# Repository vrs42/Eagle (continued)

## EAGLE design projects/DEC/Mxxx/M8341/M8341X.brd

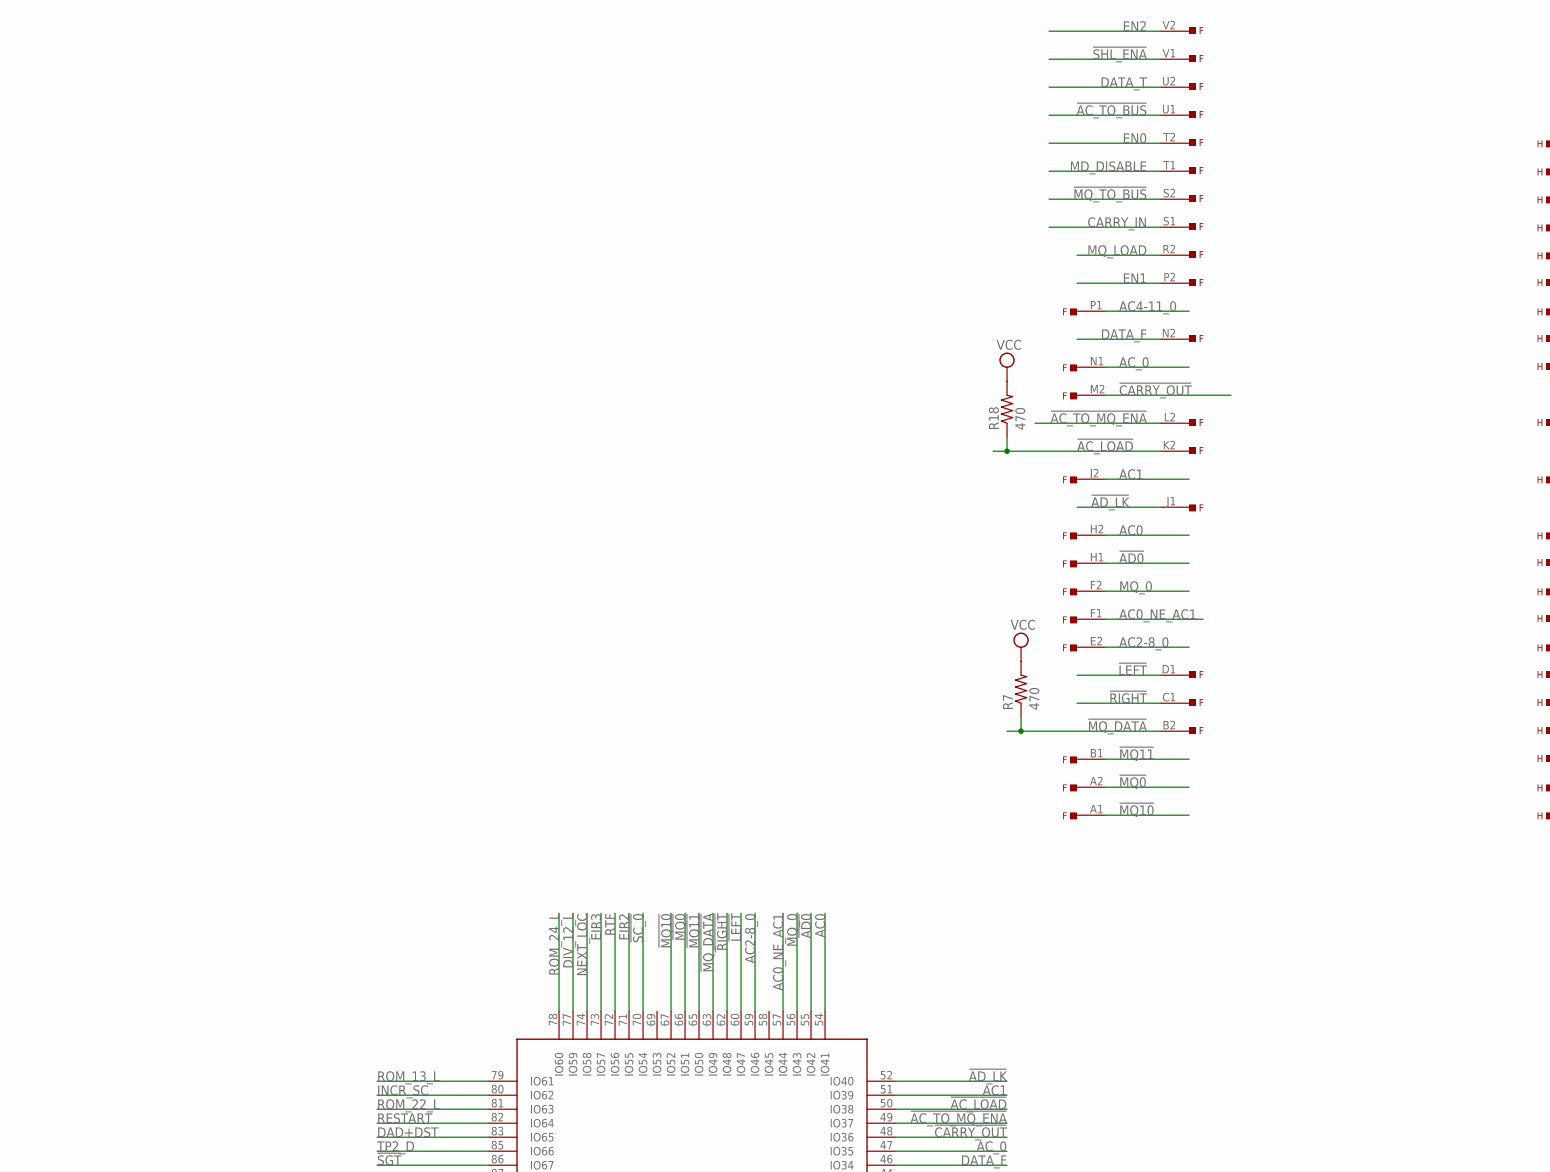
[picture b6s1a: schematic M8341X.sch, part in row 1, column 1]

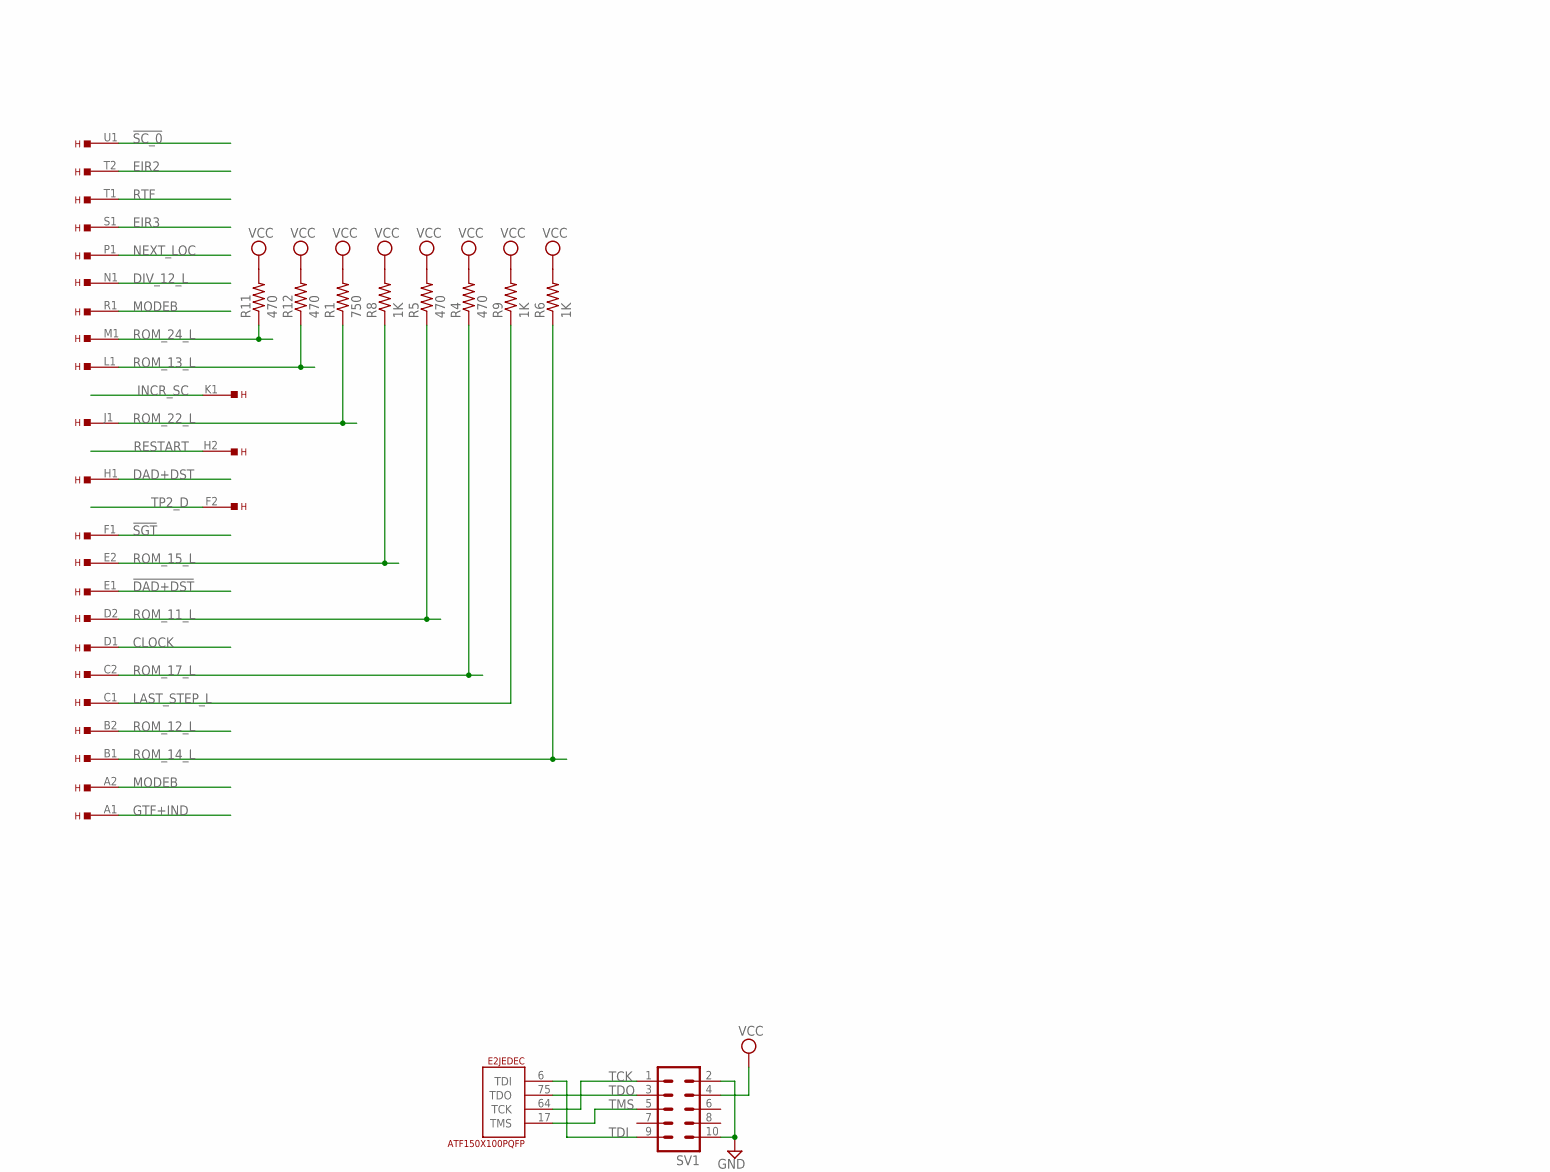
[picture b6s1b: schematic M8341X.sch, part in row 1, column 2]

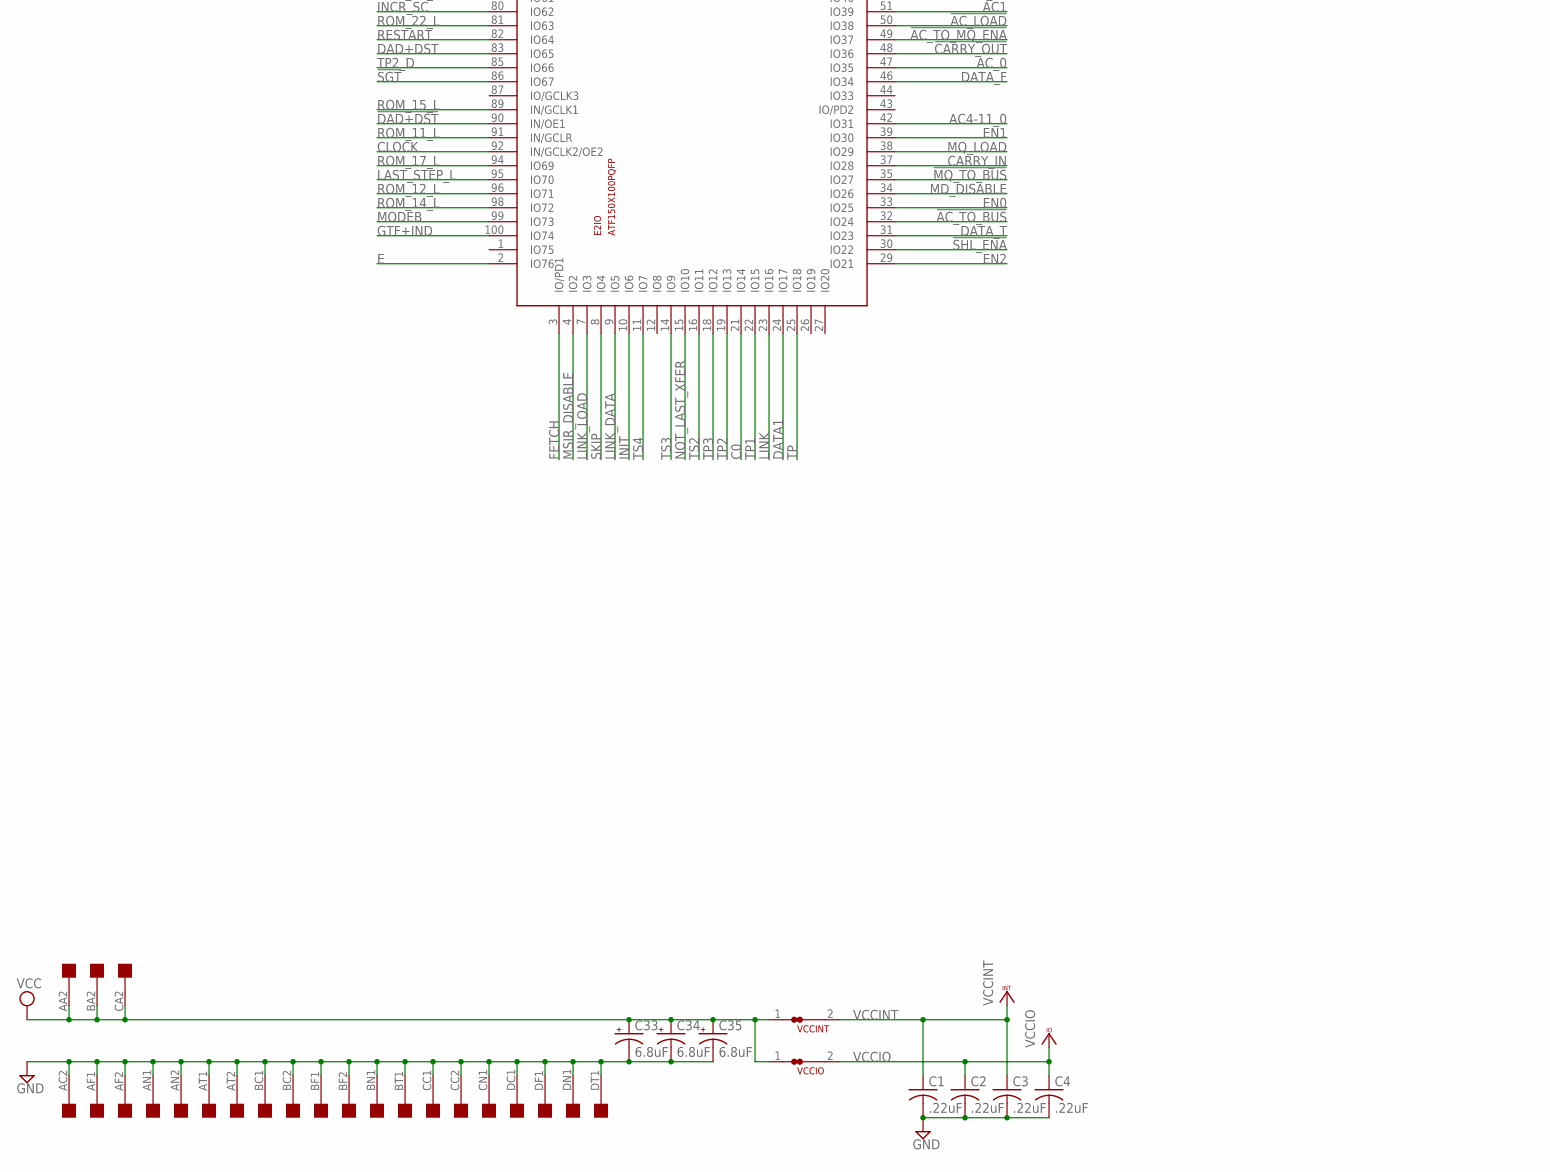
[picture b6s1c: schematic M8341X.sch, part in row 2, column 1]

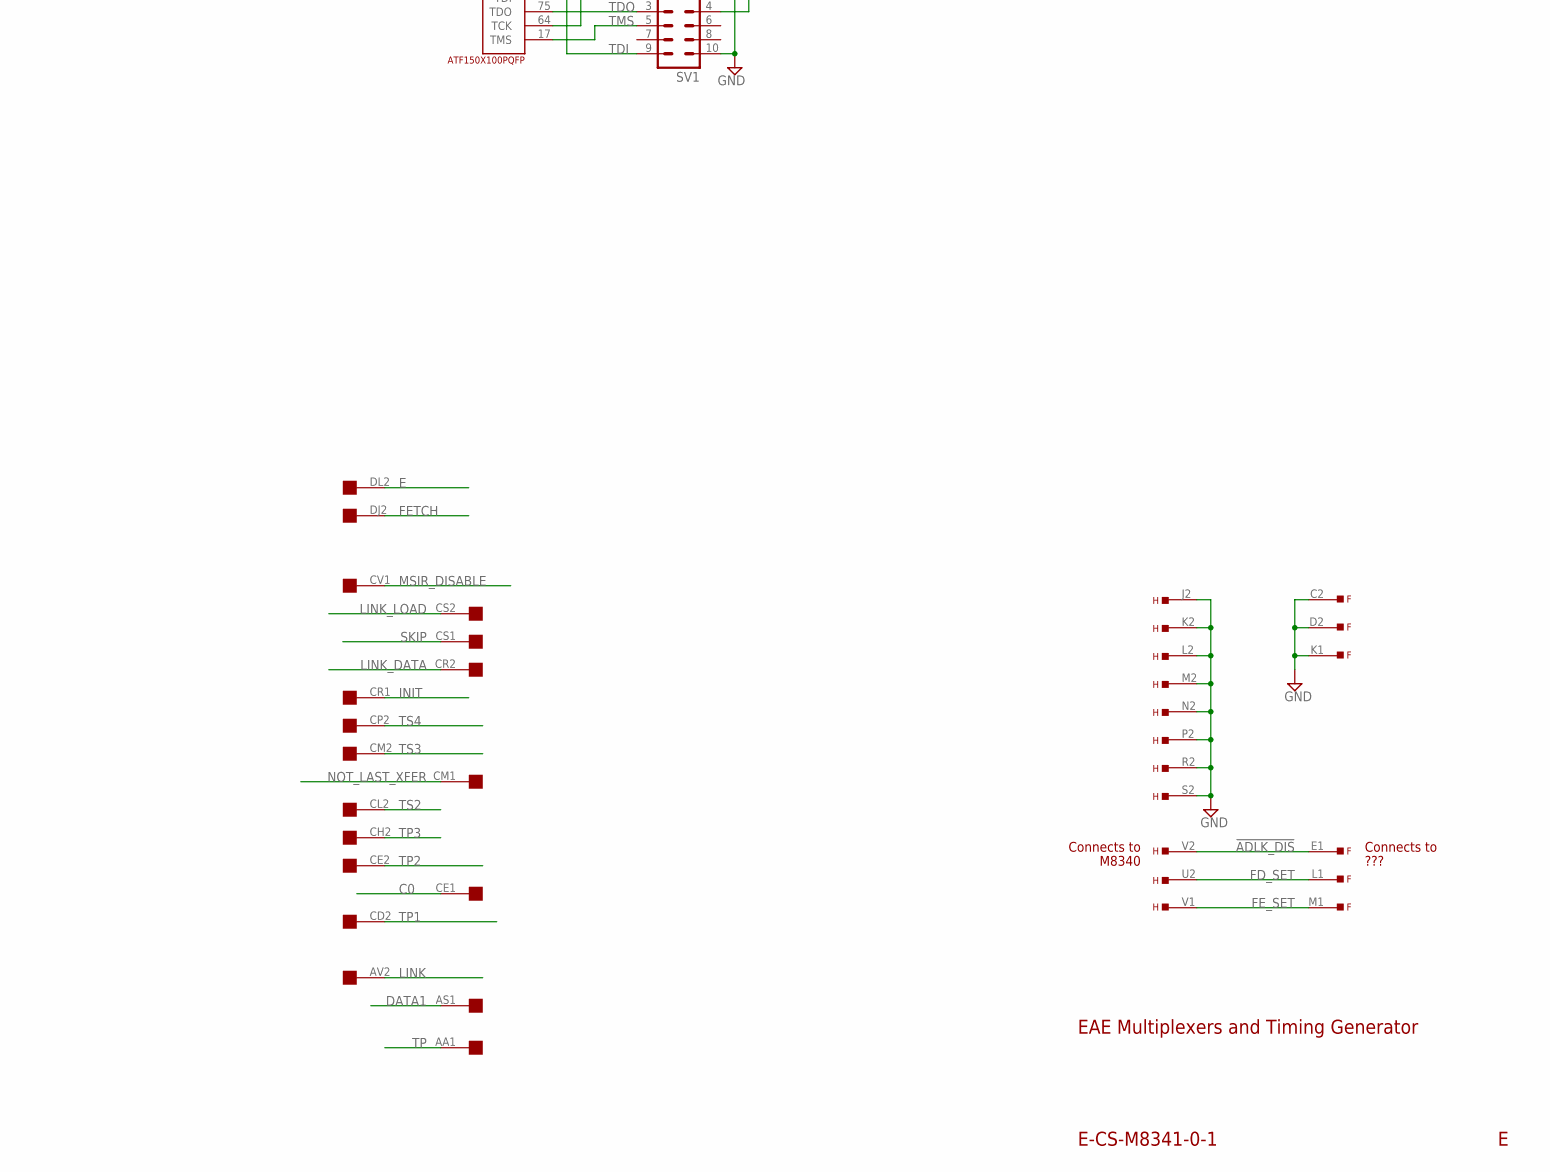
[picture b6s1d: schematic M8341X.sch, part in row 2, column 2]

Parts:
C1, C2, C3, C4: .22uF; C063-025X075
C33, C34, C35: 6.8uF; E12-8
E2: ATF150X100PQFP; PQFP-100
F: EDGE-TOP; EDGE-CON2
H: EDGE-TOP; EDGE-CON2
R1: 750; 0207/10
R4, R5, R7, R11, R12, R18: 470; 0207/10
R6, R8, R9: 1K; 0207/10
SV1: ML10
U$2: QUAD; EDGE-CON8
VCCINT: JUMPER-NC1; NC1
VCCIO: JUMPER-NC1; NC1

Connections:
!AC_LOAD: E2.50 (IO38), F.K2, R18.1
!AC_TO_BUS: E2.32 (IO24), F.U1
!AC_TO_MQ_ENA: E2.49 (IO37), F.L2
!AD0: E2.55 (IO42), F.H1
!ADLK_DIS: F.E1, H.V2
!AD_LK: E2.52 (IO40), F.J1
!CARRY_OUT: E2.48 (IO36), F.M2
!DAD+DST: E2.90 (IN/OE1), H.E1
!LEFT: E2.60 (IO47), F.D1
!MQ0: E2.66 (IO51), F.A2
!MQ10: E2.67 (IO52), F.A1
!MQ11: E2.65 (IO50), F.B1
!MQ_DATA: E2.63 (IO49), F.B2, R7.1
!MQ_TO_BUS: E2.35 (IO27), F.S2
!RIGHT: E2.62 (IO48), F.C1
!SC_0: E2.70 (IO54), H.U1
!SGT: E2.86 (IO67), H.F1
!SHL_ENA: E2.30 (IO22), F.V1
AC0: E2.54 (IO41), F.H2
AC0_NE_AC1: E2.57 (IO44), F.F1
AC1: E2.51 (IO39), F.J2
AC2-8_0: E2.59 (IO46), F.E2
AC4-11_0: E2.42 (IO31), F.P1
AC_0: E2.47 (IO35), F.N1
C0: E2.21 (IO14), U$2.CE1
CARRY_IN: E2.37 (IO28), F.S1
CLOCK: E2.92 (IN/GCLK2/OE2), H.D1
DAD+DST: E2.83 (IO65), H.H1
DATA1: E2.24 (IO17), U$2.AS1
DATA_F: E2.46 (IO34), F.N2
DATA_T: E2.31 (IO23), F.U2
DIV_12_L: E2.77 (IO59), H.N1
E: E2.2 (IO76), U$2.DL2
EIR2: E2.71 (IO55), H.T2
EIR3: E2.73 (IO57), H.S1
EN0: E2.33 (IO25), F.T2
EN1: E2.39 (IO30), F.P2
EN2: E2.29 (IO21), F.V2
FD_SET: F.L1, H.U2
FETCH: E2.3 (IO/PD1), U$2.DJ2
FE_SET: F.M1, H.V1
GND: C1.2, C2.2, C3.2, C4.2, C33.-, C34.-, C35.-, E2.13 (GND), E2.28 (GND), E2.40 (GND), E2.45 (GND), E2.61 (GND), E2.76 (GND), E2.88 (GND), E2.97 (GND), F.C2, F.D2, F.K1, H.J2, H.K2, H.L2, H.M2, H.N2, H.P2, H.R2, H.S2, SV1.2, SV1.10, U$2.AC2, U$2.AF1, U$2.AF2, U$2.AN1, U$2.AN2, U$2.AT1, U$2.AT2, U$2.BC1, U$2.BC2, U$2.BF1, U$2.BF2, U$2.BN1, U$2.BT1, U$2.CC1, U$2.CC2, U$2.CN1, U$2.DC1, U$2.DF1, U$2.DN1, U$2.DT1
GTF+IND: E2.100 (IO74), H.A1
INCR_SC: E2.80 (IO62), H.K1
INIT: E2.10 (IO6), U$2.CR1
LAST_STEP_L: E2.95 (IO70), H.C1, R9.1
LINK: E2.23 (IO16), U$2.AV2
LINK_DATA: E2.9 (IO5), U$2.CR2
LINK_LOAD: E2.7 (IO3), U$2.CS2
MD_DISABLE: E2.34 (IO26), F.T1
MODEB: E2.99 (IO73), H.A2, H.R1
MQ_0: E2.56 (IO43), F.F2
MQ_LOAD: E2.38 (IO29), F.R2
MSIR_DISABLE: E2.4 (IO2), U$2.CV1
NEXT_LOC: E2.74 (IO58), H.P1
NOT_LAST_XFER: E2.15 (IO10), U$2.CM1
RESTART: E2.82 (IO64), H.H2
ROM_11_L: E2.91 (IN/GCLR), H.D2, R5.1
ROM_12_L: E2.96 (IO71), H.B2
ROM_13_L: E2.79 (IO61), H.L1, R12.1
ROM_14_L: E2.98 (IO72), H.B1, R6.1
ROM_15_L: E2.89 (IN/GCLK1), H.E2, R8.1
ROM_17_L: E2.94 (IO69), H.C2, R4.1
ROM_22_L: E2.81 (IO63), H.J1, R1.1
ROM_24_L: E2.78 (IO60), H.M1, R11.1
RTF: E2.72 (IO56), H.T1
SKIP: E2.8 (IO4), U$2.CS1
TCK: E2.64 (TCK), SV1.1
TDI: E2.6 (TDI), SV1.9
TDO: E2.75 (TDO), SV1.3
TMS: E2.17 (TMS), SV1.5
TP: E2.25 (IO18), U$2.AA1
TP1: E2.22 (IO15), U$2.CD2
TP2: E2.19 (IO13), U$2.CE2
TP2_D: E2.85 (IO66), H.F2
TP3: E2.18 (IO12), U$2.CH2
TS2: E2.16 (IO11), U$2.CL2
TS3: E2.14 (IO9), U$2.CM2
TS4: E2.11 (IO7), U$2.CP2
VCC: C33.+, C34.+, C35.+, R1.2, R4.2, R5.2, R6.2, R7.2, R8.2, R9.2, R11.2, R12.2, R18.2, SV1.4, U$2.AA2, U$2.BA2, U$2.CA2, VCCINT.1, VCCIO.1
VCCINT: C1.1, C3.1, E2.41 (VCCINT), E2.93 (VCCINT), VCCINT.2
VCCIO: C2.1, C4.1, E2.5 (VCCIO), E2.20 (VCCIO), E2.36 (VCCIO), E2.53 (VCCIO), E2.68 (VCCIO), E2.84 (VCCIO), VCCIO.2

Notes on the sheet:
E-CS-M8341-0-1
EAE Multiplexers and Timing Generator
???
Connects to
M8340

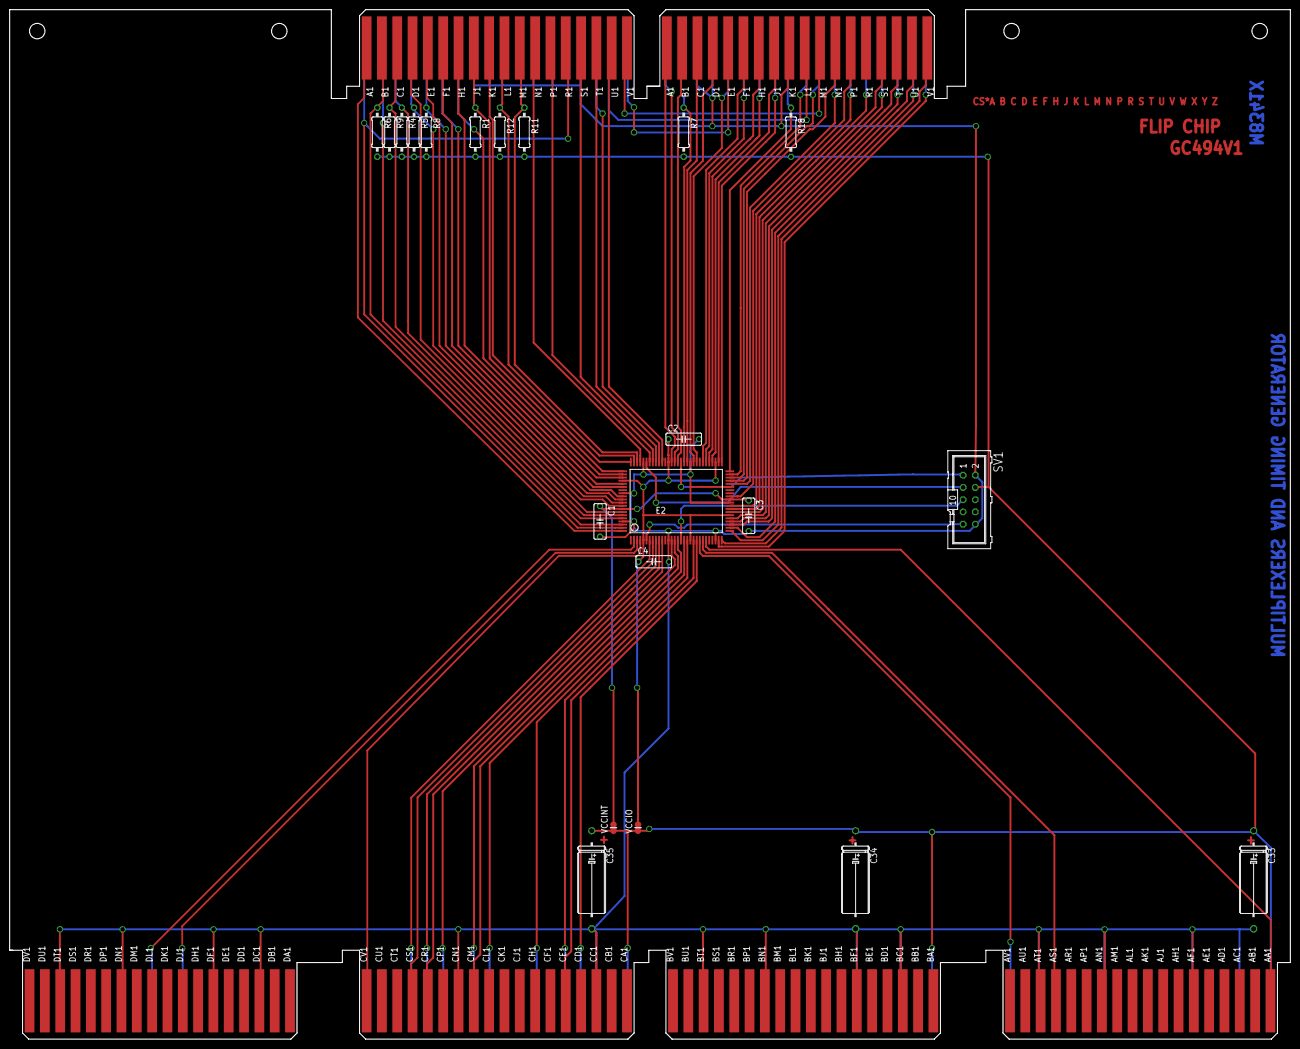
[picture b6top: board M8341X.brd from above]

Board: 2 copper layers, 265.4 x 213.4 mm, 24 parts (0 on the bottom side), 82 nets.

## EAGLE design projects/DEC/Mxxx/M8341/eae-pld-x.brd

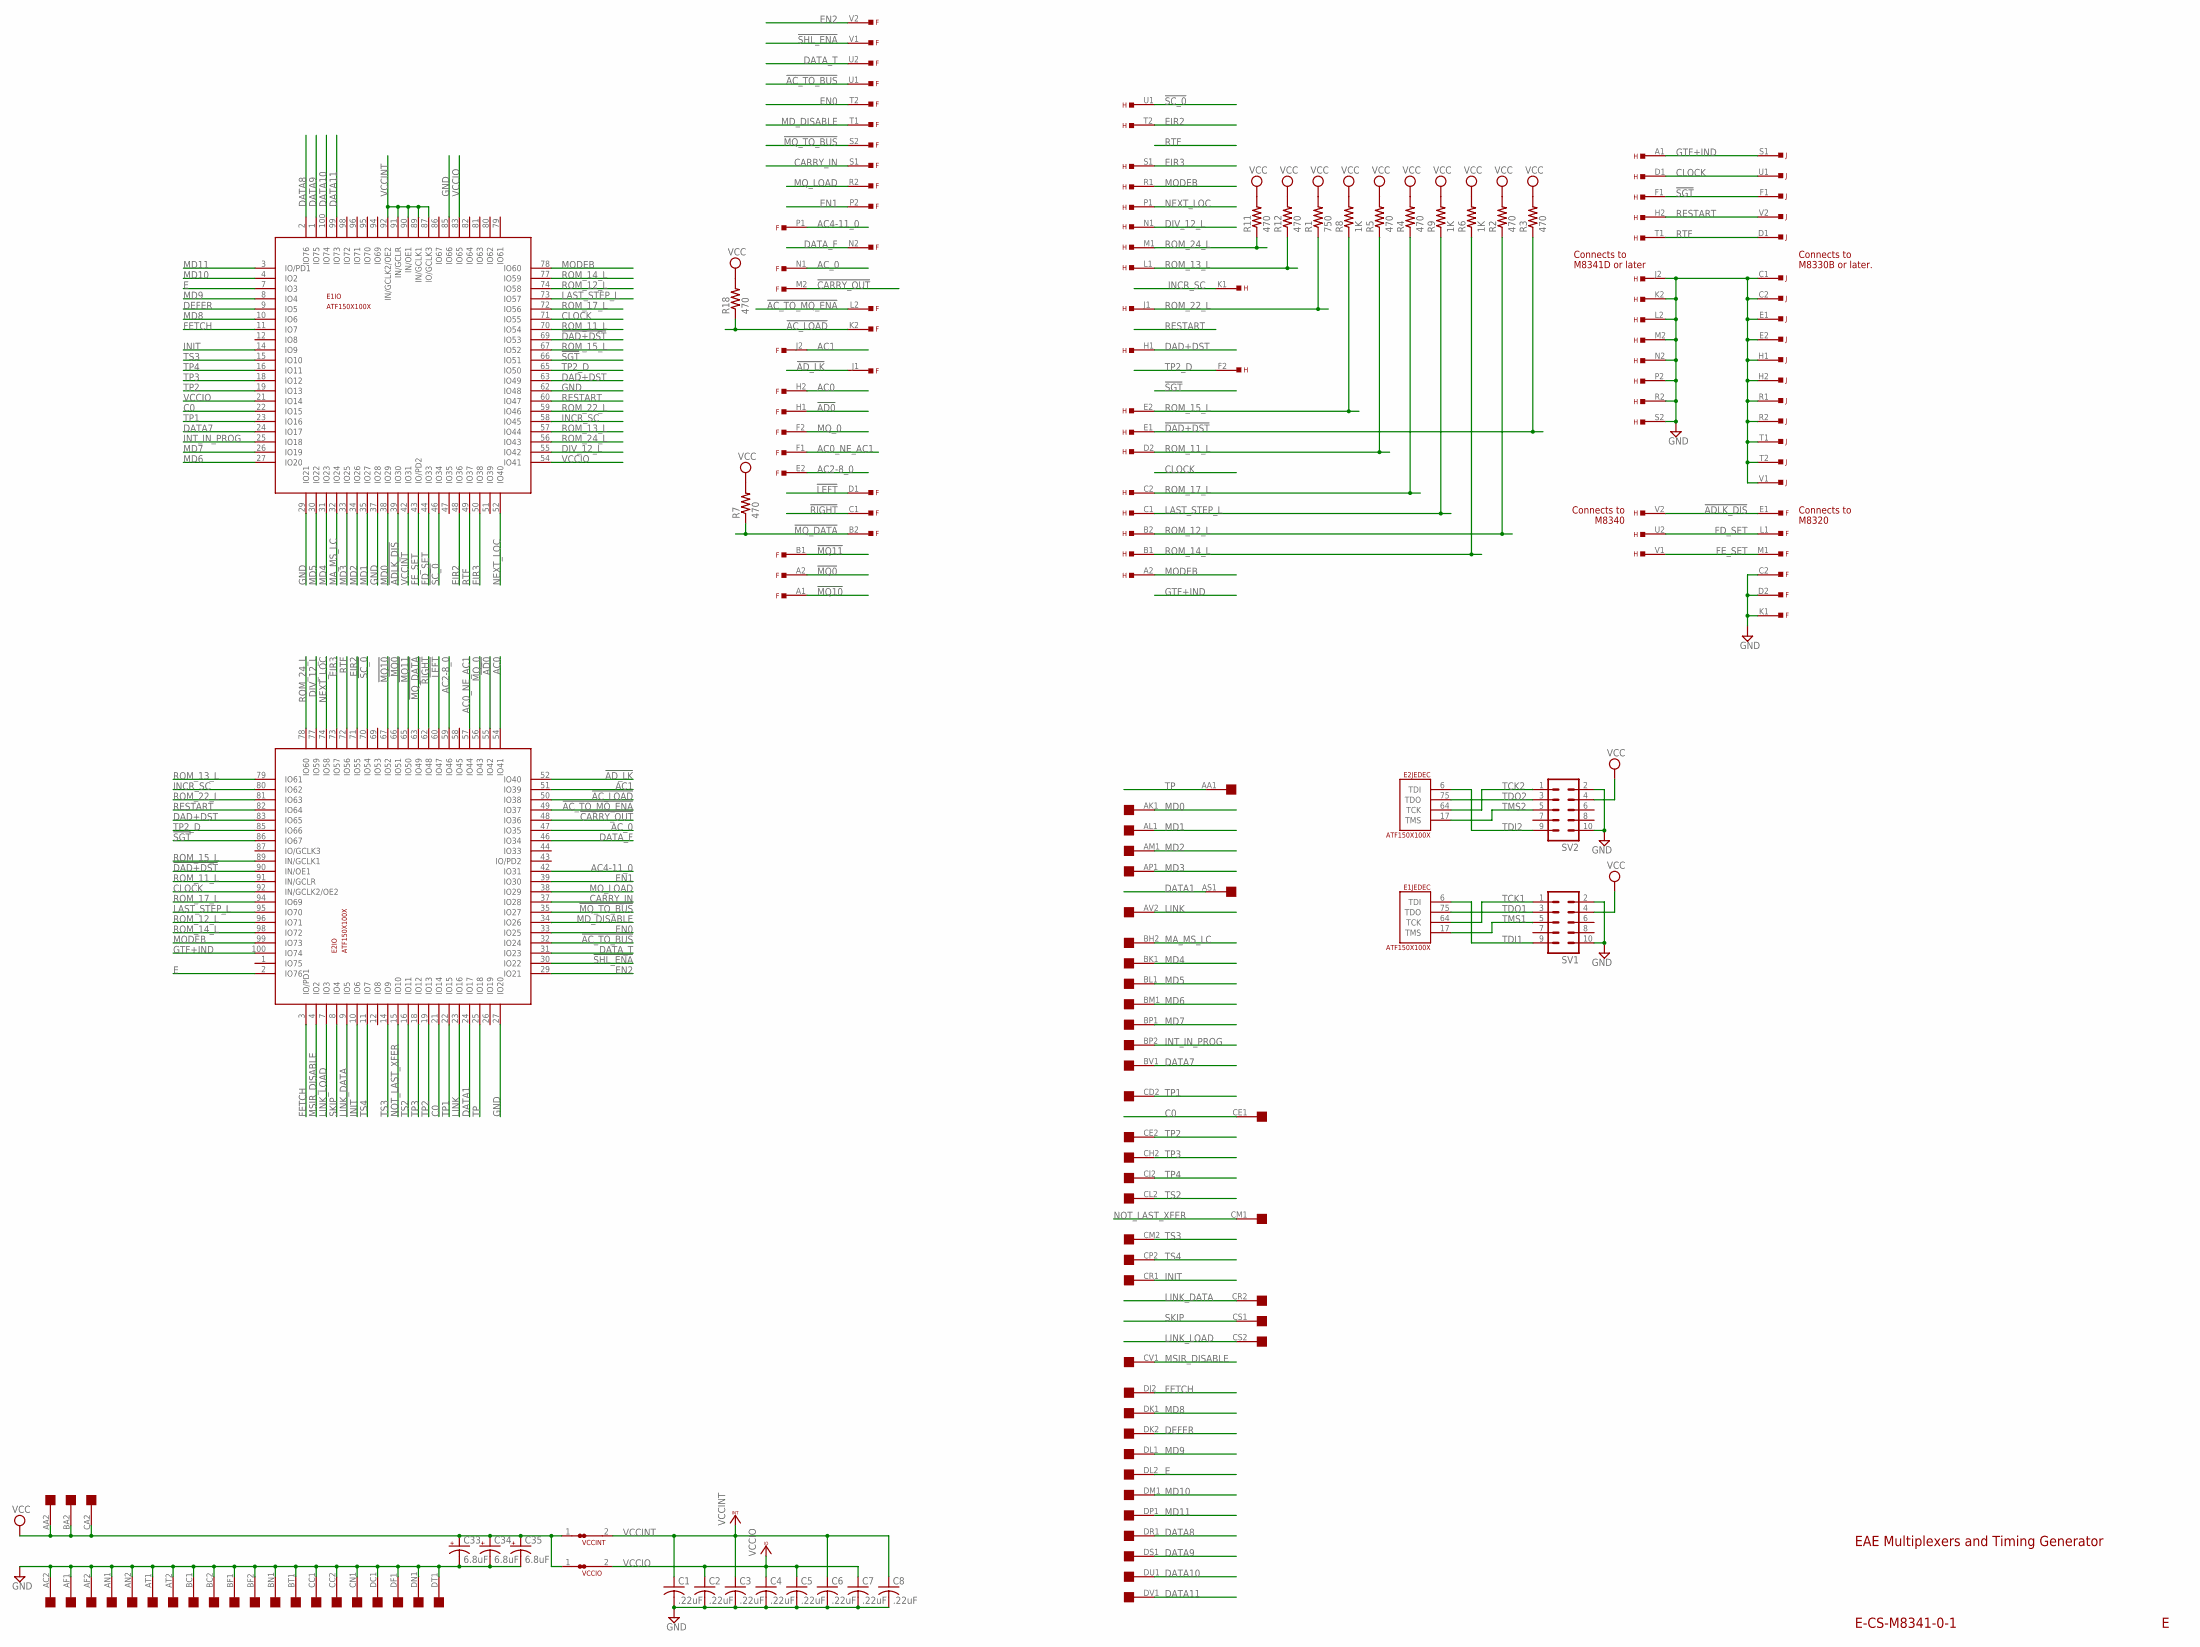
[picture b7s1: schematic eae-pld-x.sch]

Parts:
C1, C2, C3, C4, C5, C6, C7, C8: .22uF; C063-025X075
C33, C34, C35: 6.8uF; E12-8
E1, E2: ATF150X100X; TH100B
F: EDGE-TOP; EDGE-CON2
H: EDGE-TOP; EDGE-CON2
J: EDGE-TOP; EDGE-CON2
R1: 750; 0207/10
R2, R3, R4, R5, R7, R11, R12, R18: 470; 0207/10
R6, R8, R9: 1K; 0207/10
SV1, SV2: ML10
U$1: QUAD; EDGE-CON8
VCCINT: JUMPER-NC1; NC1
VCCIO: JUMPER-NC1; NC1

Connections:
!AC_LOAD: E2.50 (IO38), F.K2, R18.1
!AC_TO_BUS: E2.32 (IO24), F.U1
!AC_TO_MQ_ENA: E2.49 (IO37), F.L2
!AD0: E2.55 (IO42), F.H1
!ADLK_DIS: E1.39 (IO30), F.E1, H.V2
!AD_LK: E2.52 (IO40), F.J1
!CARRY_OUT: E2.48 (IO36), F.M2
!DAD+DST: E1.69 (IO53), E2.90 (IN/OE1), H.E1, R3.1
!LEFT: E2.60 (IO47), F.D1
!MQ0: E2.66 (IO51), F.A2
!MQ10: E2.67 (IO52), F.A1
!MQ11: E2.65 (IO50), F.B1
!MQ_DATA: E2.63 (IO49), F.B2, R7.1
!MQ_TO_BUS: E2.35 (IO27), F.S2
!RIGHT: E2.62 (IO48), F.C1
!SC_0: E1.46 (IO34), E2.70 (IO54), H.U1
!SGT: E1.66 (IO51), E2.86 (IO67), H.F1, J.F1
!SHL_ENA: E2.30 (IO22), F.V1
AC0: E2.54 (IO41), F.H2
AC0_NE_AC1: E2.57 (IO44), F.F1
AC1: E2.51 (IO39), F.J2
AC2-8_0: E2.59 (IO46), F.E2
AC4-11_0: E2.42 (IO31), F.P1
AC_0: E2.47 (IO35), F.N1
C0: E1.22 (IO15), E2.21 (IO14), U$1.CE1
CARRY_IN: E2.37 (IO28), F.S1
CLOCK: E1.71 (IO55), E2.92 (IN/GCLK2/OE2), H.D1, J.U1
DAD+DST: E1.63 (IO49), E2.83 (IO65), H.H1
DATA1: E2.24 (IO17), U$1.AS1
DATA7: E1.24 (IO17), U$1.BV1
DATA8: E1.2 (IO76), U$1.DR1
DATA9: E1.1 (IO75), U$1.DS1
DATA10: E1.100 (IO74), U$1.DU1
DATA11: E1.99 (IO73), U$1.DV1
DATA_F: E2.46 (IO34), F.N2
DATA_T: E2.31 (IO23), F.U2
DEFER: E1.9 (IO5), U$1.DK2
DIV_12_L: E1.55 (IO42), E2.77 (IO59), H.N1
E: E1.7 (IO3), E2.2 (IO76), U$1.DL2
EIR2: E1.48 (IO36), E2.71 (IO55), H.T2
EIR3: E1.50 (IO38), E2.73 (IO57), H.S1
EN0: E2.33 (IO25), F.T2
EN1: E2.39 (IO30), F.P2
EN2: E2.29 (IO21), F.V2
FD_SET: E1.44 (IO33), F.L1, H.U2
FETCH: E1.11 (IO7), E2.3 (IO/PD1), U$1.DJ2
FE_SET: E1.43 (IO/PD2), F.M1, H.V1
GND: C1.2, C2.2, C3.2, C4.2, C5.2, C6.2, C7.2, C8.2, C33.-, C34.-, C35.-, E1.13 (GND), E1.28 (GND), E1.29 (IO21), E1.37 (IO28), E1.40 (GND), E1.45 (GND), E1.61 (GND), E1.62 (IO48), E1.76 (GND), E1.85 (IO66), E1.88 (GND), E1.97 (GND), E1.P$24 (GND), E1.P$26 (GND), E1.P$28 (GND), E1.P$30 (GND), E2.13 (GND), E2.27 (IO20), E2.28 (GND), E2.40 (GND), E2.45 (GND), E2.61 (GND), E2.76 (GND), E2.88 (GND), E2.97 (GND), E2.P$24 (GND), E2.P$26 (GND), E2.P$28 (GND), E2.P$30 (GND), F.C2, F.D2, F.K1, H.J2, H.K2, H.L2, H.M2, H.N2, H.P2, H.R2, H.S2, J.C1, J.C2, J.E1, J.E2, J.H1, J.H2, J.R1, J.R2, J.T1, J.T2, J.V1, SV1.2, SV1.10, SV2.2, SV2.10, U$1.AC2, U$1.AF1, U$1.AF2, U$1.AN1, U$1.AN2, U$1.AT1, U$1.AT2, U$1.BC1, U$1.BC2, U$1.BF1, U$1.BF2, U$1.BN1, U$1.BT1, U$1.CC1, U$1.CC2, U$1.CN1, U$1.DC1, U$1.DF1, U$1.DN1, U$1.DT1
GTF+IND: E2.100 (IO74), H.A1, J.S1
INCR_SC: E1.58 (IO45), E2.80 (IO62), H.K1
INIT: E1.14 (IO9), E2.10 (IO6), U$1.CR1
INT_IN_PROG: E1.25 (IO18), U$1.BP2
LAST_STEP_L: E1.73 (IO57), E2.95 (IO70), H.C1, R9.1
LINK: E2.23 (IO16), U$1.AV2
LINK_DATA: E2.9 (IO5), U$1.CR2
LINK_LOAD: E2.7 (IO3), U$1.CS2
MA_MS_LC: E1.32 (IO24), U$1.BH2
MD0: E1.38 (IO29), U$1.AK1
MD1: E1.35 (IO27), U$1.AL1
MD2: E1.34 (IO26), U$1.AM1
MD3: E1.33 (IO25), U$1.AP1
MD4: E1.31 (IO23), U$1.BK1
MD5: E1.30 (IO22), U$1.BL1
MD6: E1.27 (IO20), U$1.BM1
MD7: E1.26 (IO19), U$1.BP1
MD8: E1.10 (IO6), U$1.DK1
MD9: E1.8 (IO4), U$1.DL1
MD10: E1.4 (IO2), U$1.DM1
MD11: E1.3 (IO/PD1), U$1.DP1
MD_DISABLE: E2.34 (IO26), F.T1
MODEB: E1.78 (IO60), E2.99 (IO73), H.A2, H.R1
MQ_0: E2.56 (IO43), F.F2
MQ_LOAD: E2.38 (IO29), F.R2
MSIR_DISABLE: E2.4 (IO2), U$1.CV1
NEXT_LOC: E1.52 (IO40), E2.74 (IO58), H.P1
NOT_LAST_XFER: E2.15 (IO10), U$1.CM1
RESTART: E1.60 (IO47), E2.82 (IO64), H.H2, J.V2
ROM_11_L: E1.70 (IO54), E2.91 (IN/GCLR), H.D2, R5.1
ROM_12_L: E1.74 (IO58), E2.96 (IO71), H.B2, R2.1
ROM_13_L: E1.57 (IO44), E2.79 (IO61), H.L1, R12.1
ROM_14_L: E1.77 (IO59), E2.98 (IO72), H.B1, R6.1
ROM_15_L: E1.67 (IO52), E2.89 (IN/GCLK1), H.E2, R8.1
ROM_17_L: E1.72 (IO56), E2.94 (IO69), H.C2, R4.1
ROM_22_L: E1.59 (IO46), E2.81 (IO63), H.J1, R1.1
ROM_24_L: E1.56 (IO43), E2.78 (IO60), H.M1, R11.1
RTF: E1.49 (IO37), E2.72 (IO56), H.T1, J.D1
SKIP: E2.8 (IO4), U$1.CS1
TCK1: E1.64 (TCK), SV1.1
TCK2: E2.64 (TCK), SV2.1
TDI1: E1.6 (TDI), SV1.9
TDI2: E2.6 (TDI), SV2.9
TDO1: E1.75 (TDO), SV1.3
TDO2: E2.75 (TDO), SV2.3
TMS1: E1.17 (TMS), SV1.5
TMS2: E2.17 (TMS), SV2.5
TP: E2.25 (IO18), U$1.AA1
TP1: E1.23 (IO16), E2.22 (IO15), U$1.CD2
TP2: E1.19 (IO13), E2.19 (IO13), U$1.CE2
TP2_D: E1.65 (IO50), E2.85 (IO66), H.F2
TP3: E1.18 (IO12), E2.18 (IO12), U$1.CH2
TP4: E1.16 (IO11), U$1.CJ2
TS2: E2.16 (IO11), U$1.CL2
TS3: E1.15 (IO10), E2.14 (IO9), U$1.CM2
TS4: E2.11 (IO7), U$1.CP2
VCC: C33.+, C34.+, C35.+, R1.2, R2.2, R3.2, R4.2, R5.2, R6.2, R7.2, R8.2, R9.2, R11.2, R12.2, R18.2, SV1.4, SV2.4, U$1.AA2, U$1.BA2, U$1.CA2, VCCINT.1, VCCIO.1
VCCINT: C1.1, C3.1, C6.1, C8.1, E1.41 (VCCINT), E1.42 (IO31), E1.87 (IO/GCLK3), E1.89 (IN/GCLK1), E1.90 (IN/OE1), E1.91 (IN/GCLR), E1.92 (IN/GCLK2/OE2), E1.93 (VCCINT), E1.P$23 (VCCINT), E1.P$25 (VCCINT), E2.41 (VCCINT), E2.93 (VCCINT), E2.P$23 (VCCINT), E2.P$25 (VCCINT), VCCINT.2
VCCIO: C2.1, C4.1, C5.1, C7.1, E1.5 (VCCIO), E1.20 (VCCIO), E1.21 (IO14), E1.36 (VCCIO), E1.53 (VCCIO), E1.54 (IO41), E1.68 (VCCIO), E1.83 (IO65), E1.84 (VCCIO), E1.P$27 (VCCIO), E1.P$29 (VCCIO), E1.VCCIO@1 (VCCIO), E1.VCCIO@2 (VCCIO), E2.5 (VCCIO), E2.20 (VCCIO), E2.36 (VCCIO), E2.53 (VCCIO), E2.68 (VCCIO), E2.84 (VCCIO), E2.P$27 (VCCIO), E2.P$29 (VCCIO), E2.VCCIO@1 (VCCIO), E2.VCCIO@2 (VCCIO), VCCIO.2

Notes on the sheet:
E-CS-M8341-0-1
EAE Multiplexers and Timing Generator
M8320
Connects to
M8340
M8330B or later.
M8341D or later

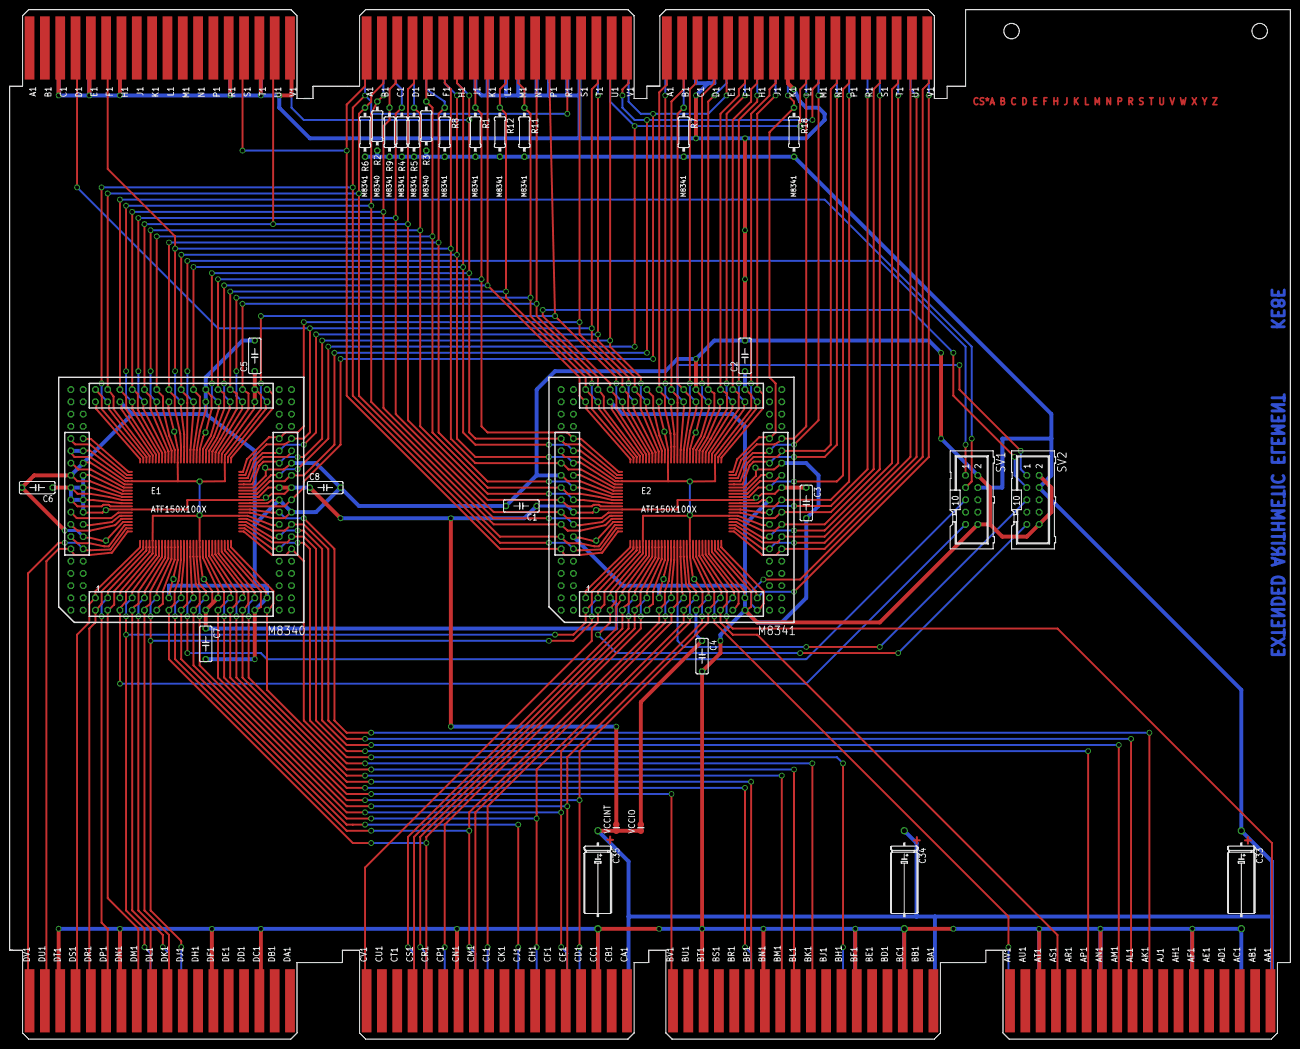
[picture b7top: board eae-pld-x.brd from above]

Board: 2 copper layers, 265.4 x 213.4 mm, 33 parts (0 on the bottom side), 107 nets.
